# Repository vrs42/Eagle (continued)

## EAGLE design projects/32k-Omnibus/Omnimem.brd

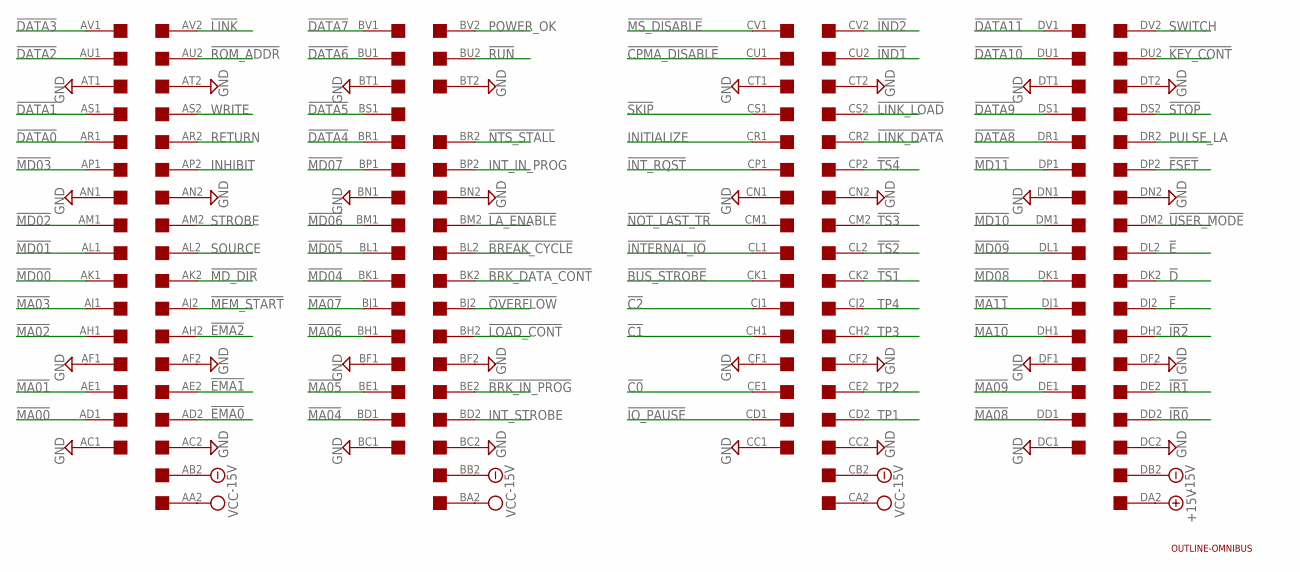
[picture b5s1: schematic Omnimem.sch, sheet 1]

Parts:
U$1: OUTLINE-OMNIBUS; OMNIBUS
U$2: QUAD; EDGE-CON8

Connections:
!BREAK_CYCLE: U$2.BL2
!BRK_DATA_CONT: U$2.BK2
!BRK_IN_PROG: U$2.BE2
!BUS_STROBE: U$2.CK1
!C0: U$2.CE1
!C1: U$2.CH1
!C2: U$2.CJ1
!CPMA_DISABLE: U$2.CU1
!D: U$2.DK2
!DATA0: U$2.AR1
!DATA1: U$2.AS1
!DATA2: U$2.AU1
!DATA3: U$2.AV1
!DATA4: U$2.BR1
!DATA5: U$2.BS1
!DATA6: U$2.BU1
!DATA7: U$2.BV1
!DATA8: U$2.DR1
!DATA9: U$2.DS1
!DATA10: U$2.DU1
!DATA11: U$2.DV1
!E: U$2.DL2
!EMA0: U$2.AD2; also elsewhere on the board
!EMA1: U$2.AE2; also elsewhere on the board
!EMA2: U$2.AH2; also elsewhere on the board
!F: U$2.DJ2
!FSET: U$2.DP2
!IND1: U$2.CU2
!IND2: U$2.CV2
!INTERNAL_IO: U$2.CL1
!INT_RQST: U$2.CP1
!IO_PAUSE: U$2.CD1
!IR0: U$2.DD2
!IR1: U$2.DE2
!IR2: U$2.DH2
!KEY_CONT: U$2.DU2
!LA_ENABLE: U$2.BM2
!LINK: U$2.AV2
!LINK_DATA: U$2.CR2
!LINK_LOAD: U$2.CS2
!LOAD_CONT: U$2.BH2
!MA00: U$2.AD1; also elsewhere on the board
!MA01: U$2.AE1; also elsewhere on the board
!MA02: U$2.AH1; also elsewhere on the board
!MA03: U$2.AJ1; also elsewhere on the board
!MA04: U$2.BD1; also elsewhere on the board
!MA05: U$2.BE1; also elsewhere on the board
!MA06: U$2.BH1; also elsewhere on the board
!MA07: U$2.BJ1; also elsewhere on the board
!MA08: U$2.DD1; also elsewhere on the board
!MA09: U$2.DE1; also elsewhere on the board
!MA10: U$2.DH1; also elsewhere on the board
!MA11: U$2.DJ1; also elsewhere on the board
!MD00: U$2.AK1; also elsewhere on the board
!MD01: U$2.AL1; also elsewhere on the board
!MD02: U$2.AM1; also elsewhere on the board
!MD03: U$2.AP1; also elsewhere on the board
!MD04: U$2.BK1; also elsewhere on the board
!MD05: U$2.BL1; also elsewhere on the board
!MD06: U$2.BM1; also elsewhere on the board
!MD07: U$2.BP1; also elsewhere on the board
!MD08: U$2.DK1; also elsewhere on the board
!MD09: U$2.DL1; also elsewhere on the board
!MD10: U$2.DM1; also elsewhere on the board
!MD11: U$2.DP1; also elsewhere on the board
!MD_DIR: U$2.AK2
!MEM_START: U$2.AJ2
!MS_DISABLE: U$2.CV1
!NOT_LAST_TR: U$2.CM1
!NTS_STALL: U$2.BR2
!OVERFLOW: U$2.BJ2
!ROM_ADDR: U$2.AU2; also elsewhere on the board
!RUN: U$2.BU2
!SKIP: U$2.CS1
!STOP: U$2.DS2
!TS1: U$2.CK2
!TS2: U$2.CL2
!TS3: U$2.CM2
!TS4: U$2.CP2
!USER_MODE: U$2.DM2
+15V: U$2.DA2
-15V: U$2.AB2, U$2.BB2, U$2.CB2, U$2.DB2
GND: U$2.AC1, U$2.AC2, U$2.AF1, U$2.AF2, U$2.AN1, U$2.AN2, U$2.AT1, U$2.AT2, U$2.BC1, U$2.BC2, U$2.BF1, U$2.BF2, U$2.BN1, U$2.BN2, U$2.BT1, U$2.BT2, U$2.CC1, U$2.CC2, U$2.CF1, U$2.CF2, U$2.CN1, U$2.CN2, U$2.CT1, U$2.CT2, U$2.DC1, U$2.DC2, U$2.DF1, U$2.DF2, U$2.DN1, U$2.DN2, U$2.DT1, U$2.DT2; also elsewhere on the board
INHIBIT: U$2.AP2
INITIALIZE: U$2.CR1
INT_IN_PROG: U$2.BP2
INT_STROBE: U$2.BD2
POWER_OK: U$2.BV2
PULSE_LA: U$2.DR2
RETURN: U$2.AR2
SOURCE: U$2.AL2
STROBE: U$2.AM2
SWITCH: U$2.DV2
TP1: U$2.CD2
TP2: U$2.CE2
TP3: U$2.CH2
TP4: U$2.CJ2
VCC: U$2.AA2, U$2.BA2, U$2.CA2; also elsewhere on the board
WRITE: U$2.AS2; also elsewhere on the board

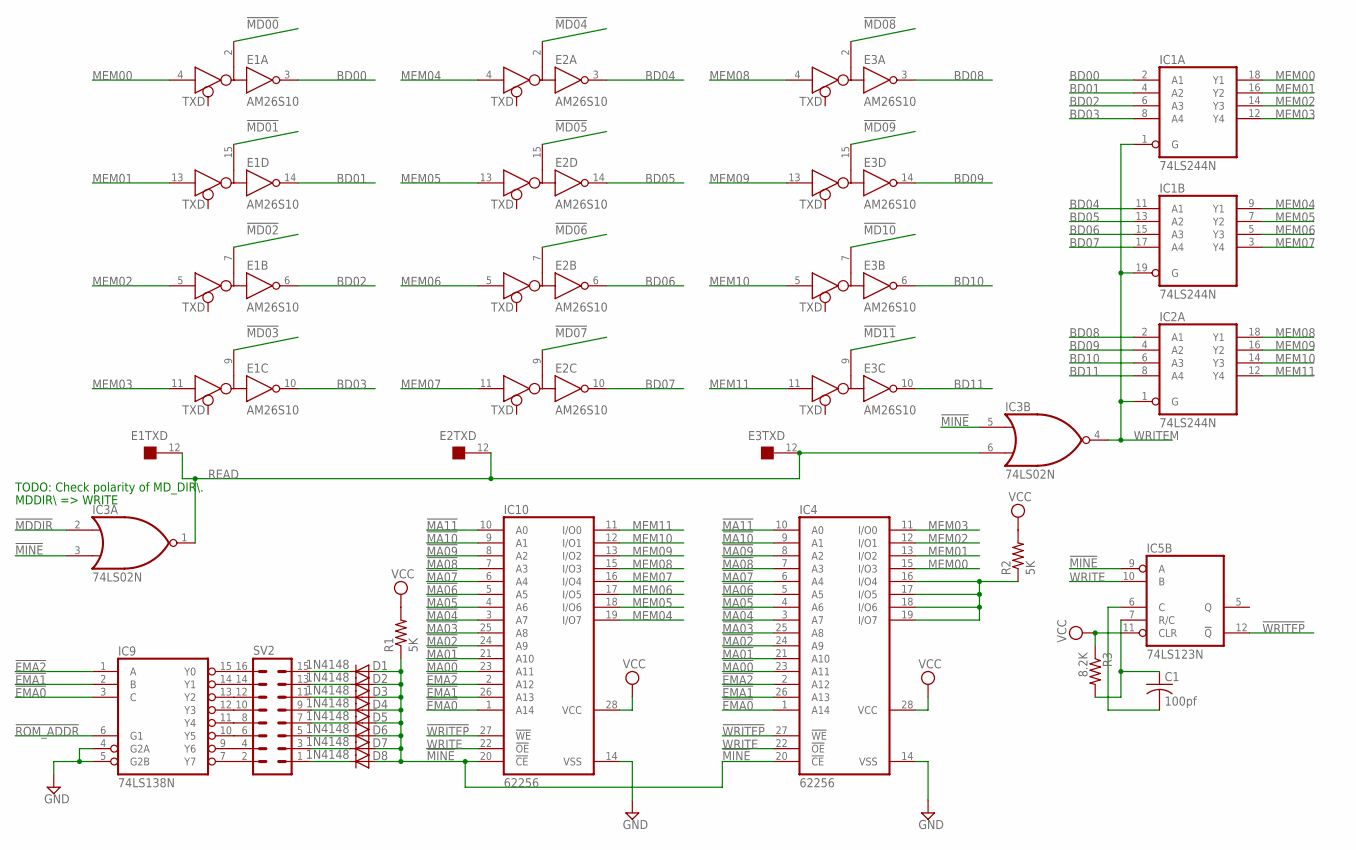
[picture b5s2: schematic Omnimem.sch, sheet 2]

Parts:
C1: 100pf; C050-025X075
D1, D2, D3, D4, D5, D6, D7, D8: 1N4148; DO35-10
E1, E2, E3: AM26S10; DIL16
IC1, IC2: 74LS244N; DIL20
IC3: 74LS02N; DIL14
IC4, IC10: 62256; DIL28-6
IC5: 74LS123N; DIL16
IC9: 74LS138N; DIL16
R1, R2: 5K; 0207/10
R3: 8.2K; 0207/10
SV2: MA08-2

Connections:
!EMA0: IC4.1 (A14), IC9.3 (C), IC10.1 (A14); also elsewhere on the board
!EMA1: IC4.26 (A13), IC9.2 (B), IC10.26 (A13); also elsewhere on the board
!EMA2: IC4.2 (A12), IC9.1 (A), IC10.2 (A12); also elsewhere on the board
!MA00: IC4.23 (A11), IC10.23 (A11); also elsewhere on the board
!MA01: IC4.21 (A10), IC10.21 (A10); also elsewhere on the board
!MA02: IC4.24 (A9), IC10.24 (A9); also elsewhere on the board
!MA03: IC4.25 (A8), IC10.25 (A8); also elsewhere on the board
!MA04: IC4.3 (A7), IC10.3 (A7); also elsewhere on the board
!MA05: IC4.4 (A6), IC10.4 (A6); also elsewhere on the board
!MA06: IC4.5 (A5), IC10.5 (A5); also elsewhere on the board
!MA07: IC4.6 (A4), IC10.6 (A4); also elsewhere on the board
!MA08: IC4.7 (A3), IC10.7 (A3); also elsewhere on the board
!MA09: IC4.8 (A2), IC10.8 (A2); also elsewhere on the board
!MA10: IC4.9 (A1), IC10.9 (A1); also elsewhere on the board
!MA11: IC4.10 (A0), IC10.10 (A0); also elsewhere on the board
!MD00: E1.2 (B); also elsewhere on the board
!MD01: E1.15 (B); also elsewhere on the board
!MD02: E1.7 (B); also elsewhere on the board
!MD03: E1.9 (B); also elsewhere on the board
!MD04: E2.2 (B); also elsewhere on the board
!MD05: E2.15 (B); also elsewhere on the board
!MD06: E2.7 (B); also elsewhere on the board
!MD07: E2.9 (B); also elsewhere on the board
!MD08: E3.2 (B); also elsewhere on the board
!MD09: E3.15 (B); also elsewhere on the board
!MD10: E3.7 (B); also elsewhere on the board
!MD11: E3.9 (B); also elsewhere on the board
!MDDIR: IC3.2 (I0)
!MINE: D1.A, D2.A, D3.A, D4.A, D5.A, D6.A, D7.A, D8.A, IC3.3 (I1), IC3.5 (I0), IC4.20 (!CE), IC5.9 (A), IC10.20 (!CE), R1.1
!ROM_ADDR: IC9.6 (G1); also elsewhere on the board
!WRITEP: IC4.27 (!WE), IC5.12 (!Q), IC10.27 (!WE)
BD00: E1.3 (R), IC1.2 (A1)
BD01: E1.14 (R), IC1.4 (A2)
BD02: E1.6 (R), IC1.6 (A3)
BD03: E1.10 (R), IC1.8 (A4)
BD04: E2.3 (R), IC1.11 (A1)
BD05: E2.14 (R), IC1.13 (A2)
BD06: E2.6 (R), IC1.15 (A3)
BD07: E2.10 (R), IC1.17 (A4)
BD08: E3.3 (R), IC2.2 (A1)
BD09: E3.14 (R), IC2.4 (A2)
BD10: E3.6 (R), IC2.6 (A3)
BD11: E3.10 (R), IC2.8 (A4)
GND: E1.1 (GND), E1.8 (GND), E2.1 (GND), E2.8 (GND), E3.1 (GND), E3.8 (GND), IC1.10 (GND), IC2.10 (GND), IC3.7 (GND), IC4.14 (VSS), IC5.8 (GND), IC9.4 (G2A), IC9.5 (G2B), IC9.8 (GND), IC10.14 (VSS); also elsewhere on the board
MEM00: E1.4 (D), IC1.18 (Y1), IC4.15 (I/O3)
MEM01: E1.13 (D), IC1.16 (Y2), IC4.13 (I/O2)
MEM02: E1.5 (D), IC1.14 (Y3), IC4.12 (I/O1)
MEM03: E1.11 (D), IC1.12 (Y4), IC4.11 (I/O0)
MEM04: E2.4 (D), IC1.9 (Y1), IC10.19 (I/O7)
MEM05: E2.13 (D), IC1.7 (Y2), IC10.18 (I/O6)
MEM06: E2.5 (D), IC1.5 (Y3), IC10.17 (I/O5)
MEM07: E2.11 (D), IC1.3 (Y4), IC10.16 (I/O4)
MEM08: E3.4 (D), IC2.18 (Y1), IC10.15 (I/O3)
MEM09: E3.13 (D), IC2.16 (Y2), IC10.13 (I/O2)
MEM10: E3.5 (D), IC2.14 (Y3), IC10.12 (I/O1)
MEM11: E3.11 (D), IC2.12 (Y4), IC10.11 (I/O0)
unnamed: IC9.7 (Y7), SV2.2
unnamed: IC9.9 (Y6), SV2.4
unnamed: IC9.10 (Y5), SV2.6
unnamed: IC9.11 (Y4), SV2.8
unnamed: IC9.12 (Y3), SV2.10
unnamed: IC9.13 (Y2), SV2.12
unnamed: IC9.14 (Y1), SV2.14
unnamed: IC9.15 (Y0), SV2.16
unnamed: C1.1, IC5.7 (R/C), R3.2
unnamed: D8.C, SV2.1
unnamed: D7.C, SV2.3
unnamed: D6.C, SV2.5
unnamed: D5.C, SV2.7
unnamed: D4.C, SV2.9
unnamed: D3.C, SV2.11
unnamed: D2.C, SV2.13
unnamed: D1.C, SV2.15
unnamed: C1.2, IC5.6 (C)
unnamed: IC4.16 (I/O4), IC4.17 (I/O5), IC4.18 (I/O6), IC4.19 (I/O7), R2.1
READ: E1.12 (TXD), E2.12 (TXD), E3.12 (TXD), IC3.1 (O), IC3.6 (I1)
VCC: E1.16 (VCC), E2.16 (VCC), E3.16 (VCC), IC1.20 (VCC), IC2.20 (VCC), IC3.14 (VCC), IC4.28 (VCC), IC5.11 (CLR), IC5.16 (VCC), IC9.16 (VCC), IC10.28 (VCC), R1.2, R2.2, R3.1; also elsewhere on the board
WRITE: IC4.22 (!OE), IC5.10 (B), IC10.22 (!OE); also elsewhere on the board
WRITEM: IC1.1 (G), IC1.19 (G), IC2.1 (G), IC3.4 (O)

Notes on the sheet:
MDDIR\\ => WRITE
TODO: Check polarity of MD_DIR\\.

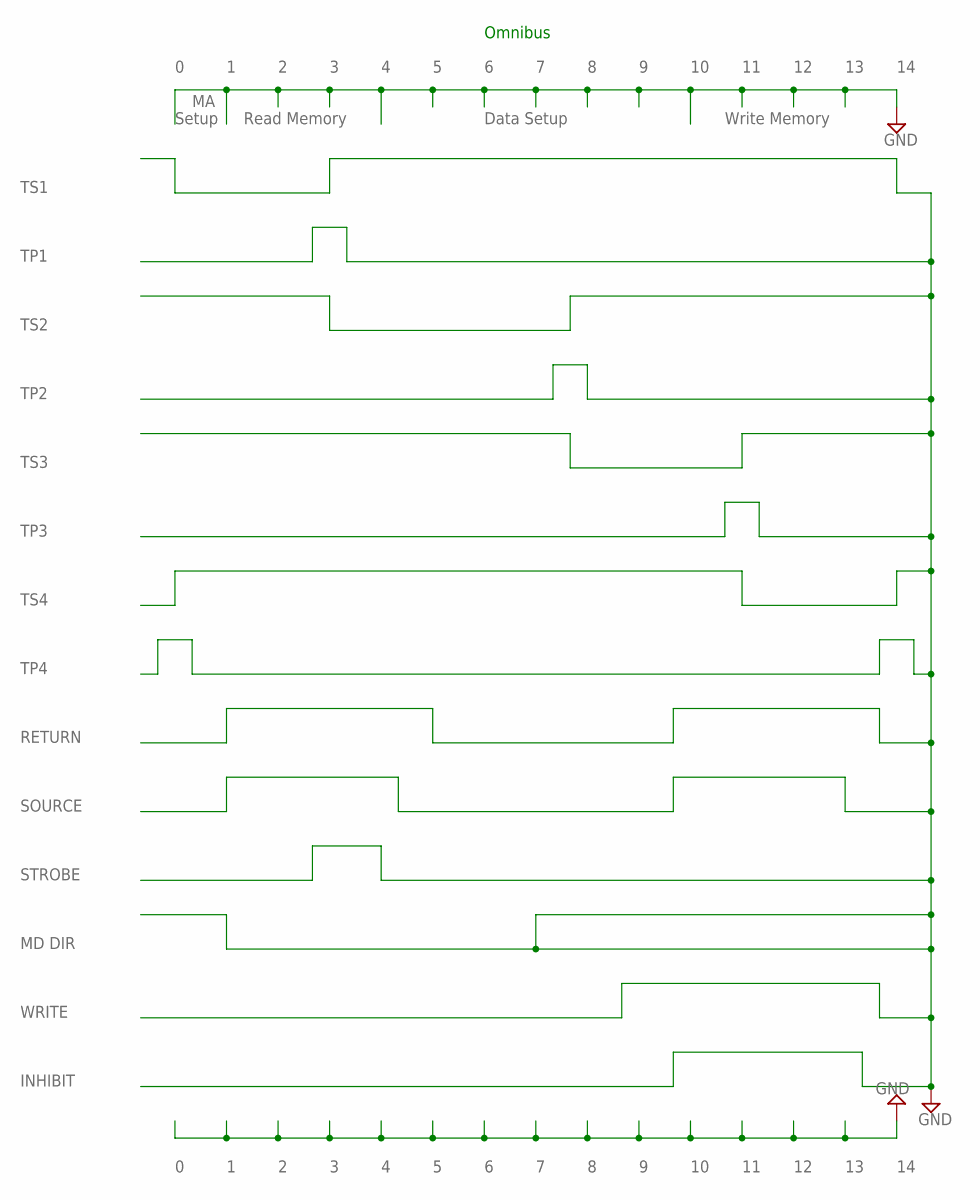
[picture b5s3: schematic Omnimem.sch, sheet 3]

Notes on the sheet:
TS1
TS2
TS3
TS4
TP1
TP2
TP3
TP4
INHIBIT
WRITE
STROBE
SOURCE
RETURN
MD DIR
Setup
Read Memory
Data Setup
Write Memory
Omnibus

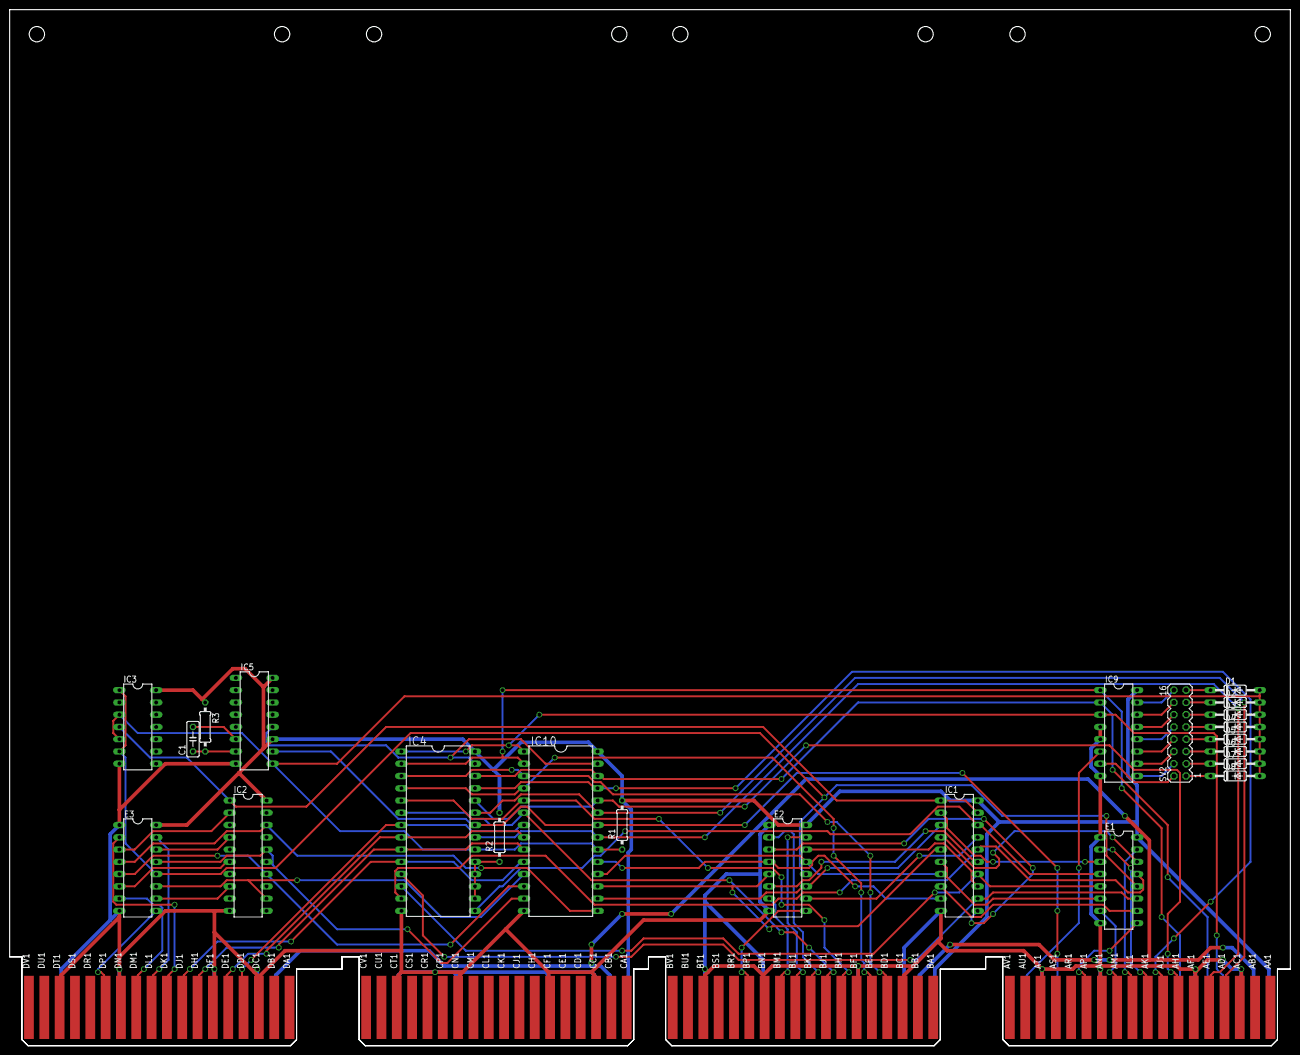
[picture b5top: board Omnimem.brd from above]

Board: 2 copper layers, 265.3 x 214.6 mm, 25 parts (0 on the bottom side), 79 nets.
